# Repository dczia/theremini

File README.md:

# Theremini

What's better than a laser theremin?  How about a laser theremin SAO?!

This SAO unfortunately does not make any noise or produce lasers, but it does have:

 - Microchip AVR attiny1616 8-bit microcontroller
 - 5 touch-sensitive buttons
 - 6 red LEDs arranged about the tape spool holes
 - Reprogrammable via UPDI via the SAO connector!

Use avr-gcc to compile the code - just run a 'make'

You'll need a UPDI programmer to program this guy.  I modded a 'ATTINY817 XPLAINED MINI' board to use as a programmer. See [this link](https://www.jsykora.info/2019/04/avr-updi-programmer-from-attiny817-xplained-mini/) for a howto.

Gerbers are included - the panel directory is the panel I actually ordered.

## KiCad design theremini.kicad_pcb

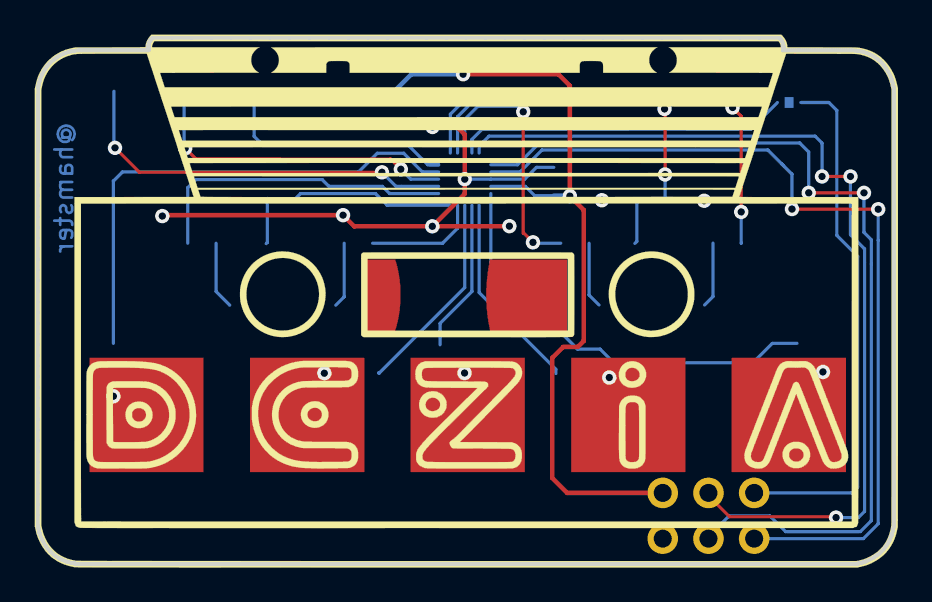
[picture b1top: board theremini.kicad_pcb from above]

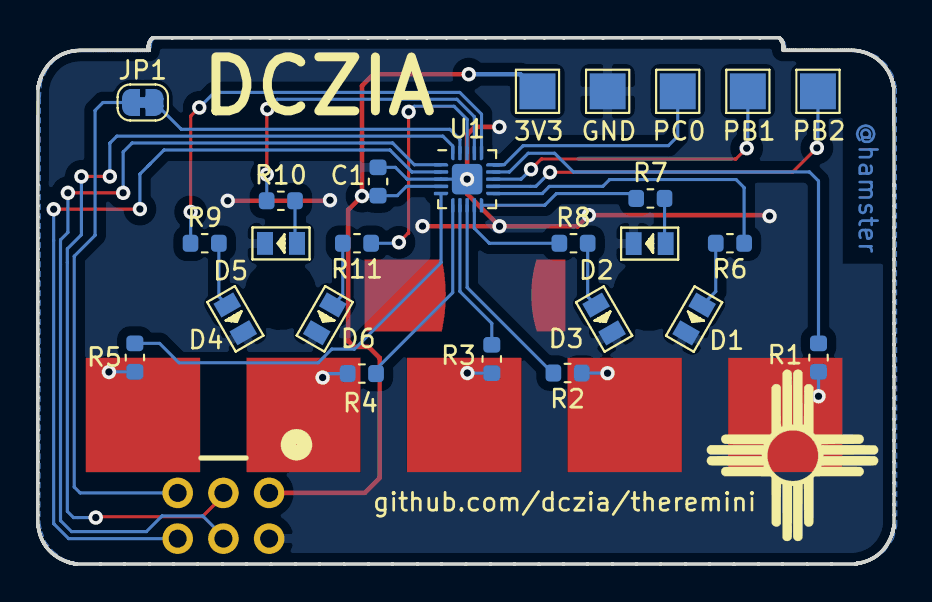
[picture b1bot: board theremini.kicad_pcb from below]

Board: 2 copper layers, 47.6 x 29.2 mm, 26 parts (25 on the bottom side), 27 nets.

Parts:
C1: C; C_0603_1608Metric
D1, D2, D3, D4, D5, D6: LED; LED-0805
J1: PB1; TestPoint_Pad_2.0x2.0mm
J2: PC0; TestPoint_Pad_2.0x2.0mm
J3: 3V3; TestPoint_Pad_2.0x2.0mm
J4: GND; TestPoint_Pad_2.0x2.0mm
J5: PB2; TestPoint_Pad_2.0x2.0mm
JP1: SolderJumper_2_Bridged; SolderJumper-2_P1.3mm_Bridged_RoundedPad1.0x1.5mm
R1, R2, R3, R4, R5: 1k; R_0603_1608Metric
R6, R7, R8, R9, R10, R11: 33R; R_0603_1608Metric
U1: ATtiny816-M; VQFN-20-1EP_3x3mm_P0.4mm_EP1.7x1.7mm
X1: Badgelife_sao_connector_v169bis; Badgelife-Shitty-v1.69bis

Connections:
+3V3: C1.1, J3.1, U1.4, X1.1
GND: C1.2, D1.1, D2.1, D3.1, D4.1, D5.1, D6.1, J4.1, U1.3, U1.21, X1.2
unnamed: D1.2, R6.2
unnamed: D2.2, R7.2
unnamed: D3.2, R8.2
unnamed: D4.2, R9.2
unnamed: D5.2, R10.2
unnamed: D6.2, R11.2
unnamed: JP1.1, X1.5
PA0: JP1.2, U1.19
PA1: U1.20, X1.3
PA2: U1.1, X1.4
PA3: U1.2, X1.6
PA4: R5.2, U1.5
PA5: R4.2, U1.6
PA6: R3.2, U1.7
PA7: R2.2, U1.8
PB0: R1.2, U1.14
PB1: J1.1, U1.13
PB2: J5.1, U1.12
PB3: R6.1, U1.11
PB4: R7.1, U1.10
PB5: R8.1, U1.9
PC0: J2.1, U1.15
PC1: R9.1, U1.16
PC2: R10.1, U1.17
PC3: R11.1, U1.18

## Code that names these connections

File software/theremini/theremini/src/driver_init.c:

/**
 * \file
 *
 * \brief Driver initialization.
 *
 (c) 2018 Microchip Technology Inc. and its subsidiaries.

    Subject to your compliance with these terms,you may use this software and
    any derivatives exclusively with Microchip products.It is your responsibility
    to comply with third party license terms applicable to your use of third party
    software (including open source software) that may accompany Microchip software.

    THIS SOFTWARE IS SUPPLIED BY MICROCHIP "AS IS". NO WARRANTIES, WHETHER
    EXPRESS, IMPLIED OR STATUTORY, APPLY TO THIS SOFTWARE, INCLUDING ANY IMPLIED
    WARRANTIES OF NON-INFRINGEMENT, MERCHANTABILITY, AND FITNESS FOR A
    PARTICULAR PURPOSE.

    IN NO EVENT WILL MICROCHIP BE LIABLE FOR ANY INDIRECT, SPECIAL, PUNITIVE,
    INCIDENTAL OR CONSEQUENTIAL LOSS, DAMAGE, COST OR EXPENSE OF ANY KIND
    WHATSOEVER RELATED TO THE SOFTWARE, HOWEVER CAUSED, EVEN IF MICROCHIP HAS
    BEEN ADVISED OF THE POSSIBILITY OR THE DAMAGES ARE FORESEEABLE. TO THE
    FULLEST EXTENT ALLOWED BY LAW, MICROCHIP'S TOTAL LIABILITY ON ALL CLAIMS IN
    ANY WAY RELATED TO THIS SOFTWARE WILL NOT EXCEED THE AMOUNT OF FEES, IF ANY,
    THAT YOU HAVE PAID DIRECTLY TO MICROCHIP FOR THIS SOFTWARE.
 *
 */

/*
 * Code generated by START.
 *
 * This file will be overwritten when reconfiguring your START project.
 * Please copy examples or other code you want to keep to a separate file
 * to avoid losing it when reconfiguring.
 */

#include "driver_init.h"
#include <system.h>
#include <tca.h>
#include <tcb.h>

void TIMER_0_initialization(void)
{

	TIMER_0_init();
}

void TIMER_1_initialization(void)
{

	TIMER_1_init();
}

/* configure pins and initialize registers */
void I2C_0_initialization(void)
{

	PA2_set_dir(
	    // <y> Pin direction
	    // <id> pad_dir
	    // <PORT_DIR_OFF"> Off
	    // <PORT_DIR_IN"> In
	    // <PORT_DIR_OUT"> Out
	    PORT_DIR_OUT);

	PA2_set_level(
	    // <y> Initial level
	    // <id> pad_initial_level
	    // <false"> Low
	    // <true"> High
	    false);

	PA2_set_pull_mode(
	    // <y> Pull configuration
	    // <id> pad_pull_config
	    // <PORT_PULL_OFF"> Off
	    // <PORT_PULL_UP"> Pull-up
	    PORT_PULL_OFF);

	PA2_set_inverted(
	    // <y> Invert I/O on pin
	    // <id> pad_invert
	    // <false"> Not inverted
	    // <true"> Inverted
	    false);

	PA2_set_isc(
	    // <y> Pin Input/Sense Configuration
	    // <id> pad_isc
	    // <PORT_ISC_INTDISABLE_gc"> Interrupt disabled but input buffer enabled
	    // <PORT_ISC_BOTHEDGES_gc"> Sense Both Edges
	    // <PORT_ISC_RISING_gc"> Sense Rising Edge
	    // <PORT_ISC_FALLING_gc"> Sense Falling Edge
	    // <PORT_ISC_INPUT_DISABLE_gc"> Digital Input Buffer disabled
	    // <PORT_ISC_LEVEL_gc"> Sense low Level
	    PORT_ISC_INTDISABLE_gc);

	/* set the alternate pin mux */
	PORTMUX.CTRLB |= PORTMUX_TWI0_bm;

	PA1_set_dir(
	    // <y> Pin direction
	    // <id> pad_dir
	    // <PORT_DIR_OFF"> Off
	    // <PORT_DIR_IN"> In
	    // <PORT_DIR_OUT"> Out
	    PORT_DIR_OUT);

	PA1_set_level(
	    // <y> Initial level
	    // <id> pad_initial_level
	    // <false"> Low
	    // <true"> High
	    false);

	PA1_set_pull_mode(
	    // <y> Pull configuration
	    // <id> pad_pull_config
	    // <PORT_PULL_OFF"> Off
	    // <PORT_PULL_UP"> Pull-up
	    PORT_PULL_OFF);

	PA1_set_inverted(
	    // <y> Invert I/O on pin
	    // <id> pad_invert
	    // <false"> Not inverted
	    // <true"> Inverted
	    false);

	PA1_set_isc(
	    // <y> Pin Input/Sense Configuration
	    // <id> pad_isc
	    // <PORT_ISC_INTDISABLE_gc"> Interrupt disabled but input buffer enabled
	    // <PORT_ISC_BOTHEDGES_gc"> Sense Both Edges
	    // <PORT_ISC_RISING_gc"> Sense Rising Edge
	    // <PORT_ISC_FALLING_gc"> Sense Falling Edge
	    // <PORT_ISC_INPUT_DISABLE_gc"> Digital Input Buffer disabled
	    // <PORT_ISC_LEVEL_gc"> Sense low Level
	    PORT_ISC_INTDISABLE_gc);

	/* set the alternate pin mux */
	PORTMUX.CTRLB |= PORTMUX_TWI0_bm;

	I2C_0_init();
}

/**
 * \brief System initialization
 */
void system_init()
{
	mcu_init();

	/* PORT setting on PA3 */

	// Set pin direction to input
	GPIO2_set_dir(PORT_DIR_IN);

	GPIO2_set_pull_mode(
	    // <y> Pull configuration
	    // <id> pad_pull_config
	    // <PORT_PULL_OFF"> Off
	    // <PORT_PULL_UP"> Pull-up
	    PORT_PULL_OFF);

	/* PORT setting on PB3 */

	// Set pin direction to output
	LED1_set_dir(PORT_DIR_OUT);

	LED1_set_level(
	    // <y> Initial level
	    // <id> pad_initial_level
	    // <false"> Low
	    // <true"> High
	    false);

	/* PORT setting on PB4 */

	// Set pin direction to output
	LED2_set_dir(PORT_DIR_OUT);

	LED2_set_level(
	    // <y> Initial level
	    // <id> pad_initial_level
	    // <false"> Low
	    // <true"> High
	    false);

	/* PORT setting on PB5 */

	// Set pin direction to output
	LED3_set_dir(PORT_DIR_OUT);

	LED3_set_level(
	    // <y> Initial level
	    // <id> pad_initial_level
	    // <false"> Low
	    // <true"> High
	    false);

	/* PORT setting on PC1 */

	// Set pin direction to output
	LED4_set_dir(PORT_DIR_OUT);

	LED4_set_level(
	    // <y> Initial level
	    // <id> pad_initial_level
	    // <false"> Low
	    // <true"> High
	    false);

	/* PORT setting on PC2 */

	// Set pin direction to output
	LED5_set_dir(PORT_DIR_OUT);

	LED5_set_level(
	    // <y> Initial level
	    // <id> pad_initial_level
	    // <false"> Low
	    // <true"> High
	    false);

	/* PORT setting on PC3 */

	// Set pin direction to output
	LED6_set_dir(PORT_DIR_OUT);

	LED6_set_level(
	    // <y> Initial level
	    // <id> pad_initial_level
	    // <false"> Low
	    // <true"> High
	    false);

	CLKCTRL_init();

	Timer_init();
	
	TIMER_1_initialization();

	CPUINT_init();

	SLPCTRL_init();

	I2C_0_initialization();

	BOD_init();
}

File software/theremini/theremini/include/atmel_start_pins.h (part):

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#include <port.h>

/**
 * \brief Set PA1 pull mode
 *
 * Configure pin to pull up, down or disable pull mode, supported pull
 * modes are defined by device used
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}

/**
 * \brief Set PA1 data direction
 *
 * Select if the pin data direction is input, output or disabled.
 * If disabled state is not possible, this function throws an assert.
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}

/**
 * \brief Set PA1 input/sense configuration
 *
 * Enable/disable PA1 digital input buffer and pin change interrupt,
 * select pin interrupt edge/level sensing mode
 *
 * \param[in] isc PORT_ISC_INTDISABLE_gc    = Iterrupt disabled but input buffer enabled
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}

/**
 * \brief Set PA1 inverted mode
 *
 * Enable or disable inverted I/O on a pin
 *
 * \param[in] inverted true  = I/O on PA1 is inverted
 *                     false = I/O on PA1 is not inverted
 */
static inline void PA1_set_inverted(const bool inverted)
{
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}

/**
 * \brief Set PA1 level
 *
 * Sets output level on a pin
 *
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}

/**
 * \brief Toggle output level on PA1
 *
 * Toggle the pin level
 */
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}

/**
 * \brief Get level on PA1
 *
 * Reads the level on a pin
 */
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}

/**
 * \brief Set PA2 pull mode
 *
 * Configure pin to pull up, down or disable pull mode, supported pull
 * modes are defined by device used
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}

/**
 * \brief Set PA2 data direction
 *
 * Select if the pin data direction is input, output or disabled.
 * If disabled state is not possible, this function throws an assert.
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}

/**
 * \brief Set PA2 input/sense configuration
 *
 * Enable/disable PA2 digital input buffer and pin change interrupt,
 * select pin interrupt edge/level sensing mode
 *
 * \param[in] isc PORT_ISC_INTDISABLE_gc    = Iterrupt disabled but input buffer enabled
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}

/**
 * \brief Set PA2 inverted mode
 *
 * Enable or disable inverted I/O on a pin
 *
 * \param[in] inverted true  = I/O on PA2 is inverted
 *                     false = I/O on PA2 is not inverted
 */
static inline void PA2_set_inverted(const bool inverted)
{
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}

/**
 * \brief Set PA2 level
 *
 * Sets output level on a pin
 *
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}

/**
 * \brief Toggle output level on PA2
 *
 * Toggle the pin level
 */
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}

/**
 * \brief Get level on PA2
 *
 * Reads the level on a pin
 */
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}

/**
 * \brief Set PA4 pull mode
 *
 * Configure pin to pull up, down or disable pull mode, supported pull
 * modes are defined by device used
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}

/**
 * \brief Set PA4 data direction
 *
 * Select if the pin data direction is input, output or disabled.
 * If disabled state is not possible, this function throws an assert.
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}

/**
 * \brief Set PA4 input/sense configuration
 *
 * Enable/disable PA4 digital input buffer and pin change interrupt,
 * select pin interrupt edge/level sensing mode
 *
 * \param[in] isc PORT_ISC_INTDISABLE_gc    = Iterrupt disabled but input buffer enabled
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}

/**
 * \brief Set PA4 inverted mode
 *
 * Enable or disable inverted I/O on a pin
 *
 * \param[in] inverted true  = I/O on PA4 is inverted
 *                     false = I/O on PA4 is not inverted
 */
static inline void PA4_set_inverted(const bool inverted)
{
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}

/**
 * \brief Set PA4 level
 *
 * Sets output level on a pin
 *
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}

/**
 * \brief Toggle output level on PA4
 *
 * Toggle the pin level
 */
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}

/**
 * \brief Get level on PA4
 *
 * Reads the level on a pin
 */
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}

/**
 * \brief Set PA5 pull mode
 *
 * Configure pin to pull up, down or disable pull mode, supported pull
 * modes are defined by device used
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}

/**
 * \brief Set PA5 data direction
 *
 * Select if the pin data direction is input, output or disabled.
 * If disabled state is not possible, this function throws an assert.
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}

/**
 * \brief Set PA5 input/sense configuration
 *
 * Enable/disable PA5 digital input buffer and pin change interrupt,
 * select pin interrupt edge/level sensing mode
 *
 * \param[in] isc PORT_ISC_INTDISABLE_gc    = Iterrupt disabled but input buffer enabled
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}

/**
 * \brief Set PA5 inverted mode
 *
 * Enable or disable inverted I/O on a pin
 *
 * \param[in] inverted true  = I/O on PA5 is inverted
 *                     false = I/O on PA5 is not inverted
 */
static inline void PA5_set_inverted(const bool inverted)
{
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}

/**
 * \brief Set PA5 level
 *
 * Sets output level on a pin
 *
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}

/**
 * \brief Toggle output level on PA5
 *
 * Toggle the pin level
 */
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}

/**
 * \brief Get level on PA5
 *
 * Reads the level on a pin
 */
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}

/**
 * \brief Set PA6 pull mode
 *
 * Configure pin to pull up, down or disable pull mode, supported pull
 * modes are defined by device used
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}

/**
 * \brief Set PA6 data direction
 *
 * Select if the pin data direction is input, output or disabled.
 * If disabled state is not possible, this function throws an assert.
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}

/**
 * \brief Set PA6 input/sense configuration
 *
 * Enable/disable PA6 digital input buffer and pin change interrupt,
 * select pin interrupt edge/level sensing mode
 *
 * \param[in] isc PORT_ISC_INTDISABLE_gc    = Iterrupt disabled but input buffer enabled
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}

/**
 * \brief Set PA6 inverted mode
 *
 * Enable or disable inverted I/O on a pin
 *
 * \param[in] inverted true  = I/O on PA6 is inverted
 *                     false = I/O on PA6 is not inverted
 */
static inline void PA6_set_inverted(const bool inverted)
{
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}

/**
 * \brief Set PA6 level
 *
 * Sets output level on a pin
 *
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}

/**
 * \brief Toggle output level on PA6
 *
 * Toggle the pin level
 */
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}

/**
 * \brief Get level on PA6
 *
 * Reads the level on a pin
 */
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}

/**
 * \brief Set PA7 pull mode
 *
 * Configure pin to pull up, down or disable pull mode, supported pull
 * modes are defined by device used
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}

/**
 * \brief Set PA7 data direction
 *
 * Select if the pin data direction is input, output or disabled.
 * If disabled state is not possible, this function throws an assert.
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}

/**
 * \brief Set PA7 input/sense configuration
 *
 * Enable/disable PA7 digital input buffer and pin change interrupt,
 * select pin interrupt edge/level sensing mode
 *
 * \param[in] isc PORT_ISC_INTDISABLE_gc    = Iterrupt disabled but input buffer enabled
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}

/**
 * \brief Set PA7 inverted mode
 *
 * Enable or disable inverted I/O on a pin
 *
 * \param[in] inverted true  = I/O on PA7 is inverted
 *                     false = I/O on PA7 is not inverted
 */
static inline void PA7_set_inverted(const bool inverted)
{
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}

/**
 * \brief Set PA7 level
 *
 * Sets output level on a pin
 *
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}

/**
 * \brief Toggle output level on PA7
 *
 * Toggle the pin level
 */
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}

/**
 * \brief Get level on PA7
 *
 * Reads the level on a pin
 */
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}

/**
 * \brief Set PB0 pull mode
 *
 * Configure pin to pull up, down or disable pull mode, supported pull
 * modes are defined by device used
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}

/**
 * \brief Set PB0 data direction
 *
 * Select if the pin data direction is input, output or disabled.
 * If disabled state is not possible, this function throws an assert.
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}

/**
 * \brief Set PB0 input/sense configuration
 *
 * Enable/disable PB0 digital input buffer and pin change interrupt,
 * select pin interrupt edge/level sensing mode
 *
 * \param[in] isc PORT_ISC_INTDISABLE_gc    = Iterrupt disabled but input buffer enabled
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}

/**
 * \brief Set PB0 inverted mode
 *
 * Enable or disable inverted I/O on a pin
 *
 * \param[in] inverted true  = I/O on PB0 is inverted
 *                     false = I/O on PB0 is not inverted
 */
static inline void PB0_set_inverted(const bool inverted)
{
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}

/**
 * \brief Set PB0 level
 *
 * Sets output level on a pin
 *
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}

/**
 * \brief Toggle output level on PB0
 *
 * Toggle the pin level
 */
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}

/**
 * \brief Get level on PB0
 *
 * Reads the level on a pin
 */
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
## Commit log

2019-07-24 Adding initial hardware design files
2019-07-24 Updated README.md Moved panel to gerber directory Fixed case on images directory
2019-07-24 Fix images
2019-08-05 Committing software for the theremini
